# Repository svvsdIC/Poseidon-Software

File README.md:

# Poseidon-Master
Contains all Poseidon related files. Please make sure to commit to your branch rather than to master.

Note: all folders contain a README.md that can be edited by the respective teams using those folders to make them easy to navigate. If your team creates additional folders please add them to this file tree.

File tree:<br/>
* Mechanical<br/>
* Electrical<br/>
* Software<br/>
  * Lulu<br/>
    * Arduino<br/>
      * LuluArduino<br/>
        * Sketches<br/>
          * Poseidon<br/>
    * Pi<br/>
  * Nemo<br/>
    * Arduino<br/>
      * NemoArduino<br/>
        * Sketches<br/>
          * Poseidon<br/>
    * Pi<br/>
* Documentation<br/>
  * Design Documents<br/>
  * Operational Documentation<br/>

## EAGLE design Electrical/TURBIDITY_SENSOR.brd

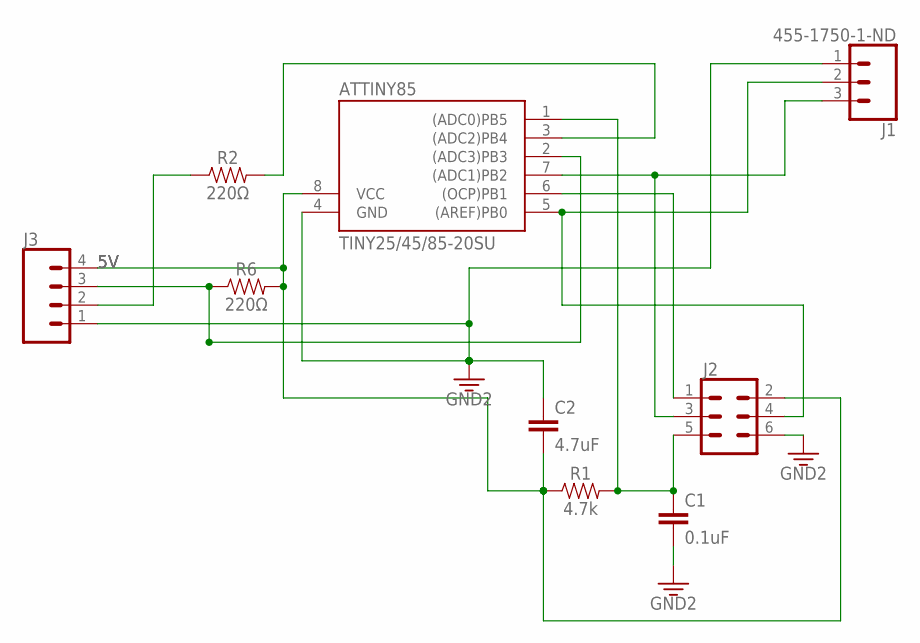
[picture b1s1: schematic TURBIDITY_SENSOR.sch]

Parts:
ATTINY85: TINY25/45/85-20SU; SOIC8
C1: 0.1uF; 0603
C2: 4.7uF; 1206
J1: 455-1750-1-ND; 1X03
J2: CONN_03X22X3_SILK_MALE_PTH; 2X3
J3: CONN_04; 1X04
R1: 4.7k; 0603
R2, R6: 220Ω; 0603

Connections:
5V: ATTINY85.8 (VCC), C2.2, J2.2, J3.4, R1.1, R6.2
DETECT: ATTINY85.2 ((ADC3)PB3), J3.3, R6.1
EMIT: ATTINY85.3 ((ADC2)PB4), R2.2
EMIT_OUT: J3.2, R2.1
GND: ATTINY85.4 (GND), C1.2, C2.1, J1.1, J2.6, J3.1
MISO: ATTINY85.6 ((OCP)PB1), J2.1
MOSI: ATTINY85.5 ((AREF)PB0), J1.2, J2.4
RESET: ATTINY85.1 ((ADC0)PB5), C1.1, J2.5, R1.2
SCK: ATTINY85.7 ((ADC1)PB2), J1.3, J2.3

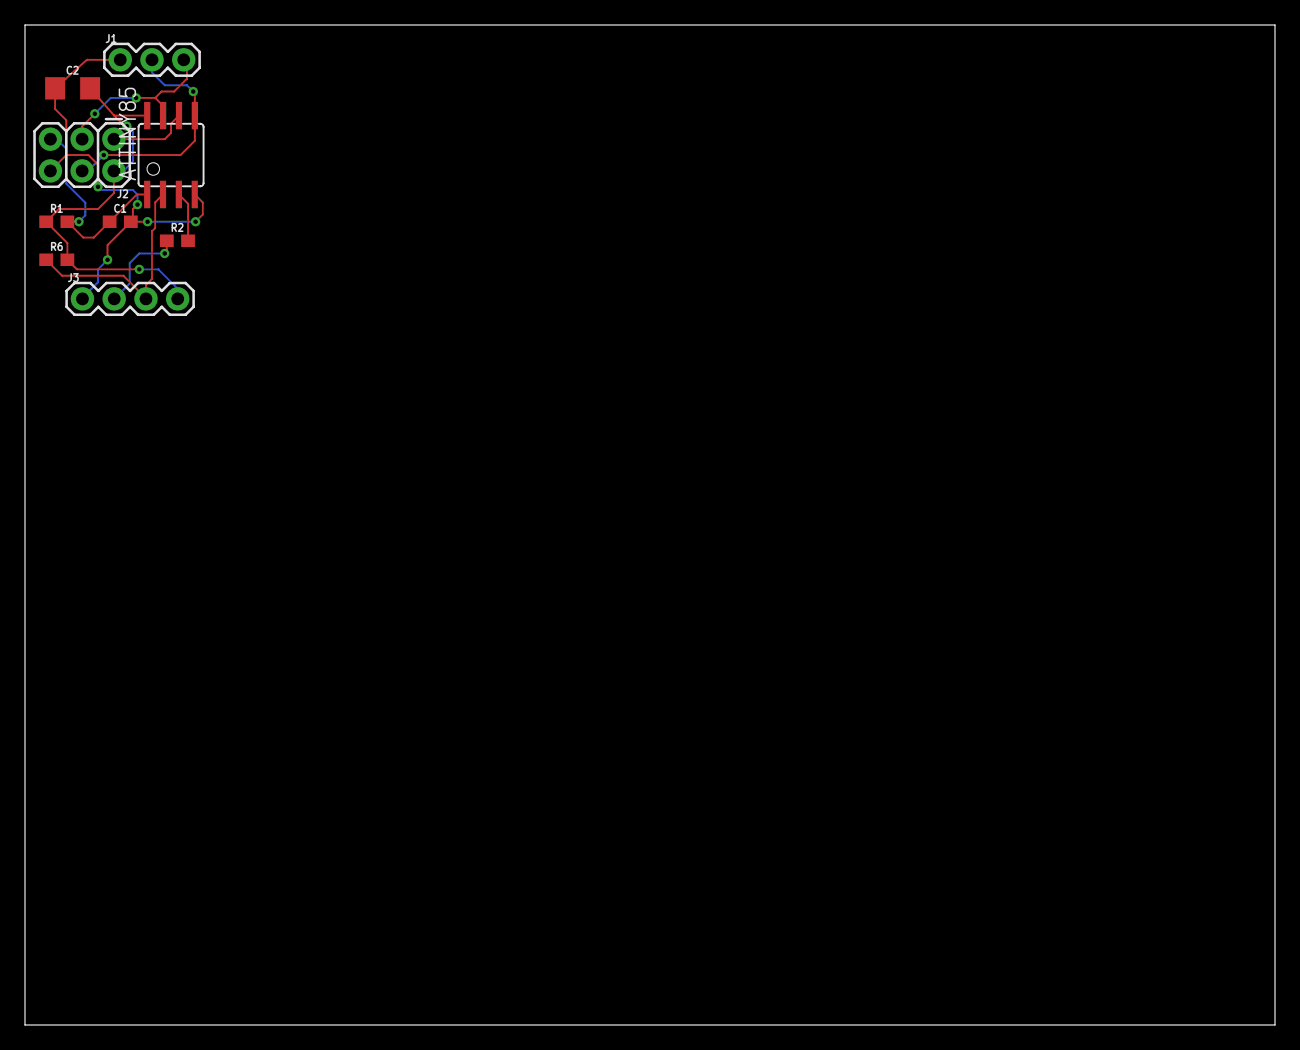
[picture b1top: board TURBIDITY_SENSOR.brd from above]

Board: 2 copper layers, 100.0 x 80.0 mm, 9 parts (0 on the bottom side), 9 nets.

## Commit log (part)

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2017-05-21 Added site specfic README, and enhanced .gitignore
2017-05-22 Ignore vim backup and swp files
2017-06-23 added poseidon-setup to be used after clone to setup additional npm dependencies
2017-11-10 Commiting Peter's work on pH sensor
2018-02-15 remove mjpeg -video plugin
2018-02-17 Changed ...js/button.js and .../button.html to pH_sensor After changing these needed to erase the cockpit cache (sudo rm -rf /usr/share/cockpit) and restart the cockpit and browser
2018-02-17 added correct hard coded url for video
2018-02-22 initial ORP and disOxy code
2018-02-22 Made ORP value change
2018-02-23 made conductivity sensor(still broken)
2018-02-26 b0be's attempt to put sensors in bottom dwelling <div>
2018-03-08 Moved the button and pH plugins to the bottom of the screen
2018-04-07 put widgets on bottom, made it run smooth
2018-04-07 made widgets look pretty
2018-04-07 Finished making a transparent background for the widgets.
2018-07-14 made the luminosity sensor. More work needs to be done because the code still has issues with button. peters fault
2018-09-22 Partial changes to button to make it temperature
2018-10-05 changes to the temperature sensor file thing because austin is complaining that I am doing it wrong
2018-10-18 made sidebysidefieldset look better
2018-11-01 The farenheit works now based of centigrade
2018-11-08 made surface temp folder. added temp arrow.
2018-11-16 Added color widget. Submerged color still needs mock data.
2019-01-25 Austin's latest.
2019-02-01 Created a bunch of random text files so folders upload
2019-02-07 Got rid of Hey.txt and added READMES
2019-02-08 Board Layout of Turbidity Sensor
    Sent to Pete for final verificaition
2019-02-08 Added X-drive
2019-02-08 Folder stuff for Davita?
2019-02-08 Merged repostories
2019-02-15 Moving Diamond Drive code to a more sensible place
    Moved from Lulu/X-Mega to Nemo/Arduino
2019-02-15 Update with slower serial polling
2019-02-20 remove unnecessary test code for figuring out server IP address
2019-03-08 Updated code, hopefully final draft
    Added analog support.
2019-03-21 Update ArduinoLight_P4
2019-04-04 Changed subColor shape to down triangle
2019-04-11 add for reference original OpenRov arduino code
2019-04-12 add the openrov-software-arduino code for reference
2019-05-23 Added surface directory which holds the code that sends surface info over bus
2019-06-09 Bump handlebars from 4.0.6 to 4.1.2 in /Software/Nemo/Pi
    Bumps [handlebars](https://github.com/wycats/handlebars.js) from 4.0.6 to 4.1.2.
    - [Release notes](https://github.com/wycats/handlebars.js/releases)
    - [Changelog](https://github.com/wycats/handlebars.js/blob/master/release-notes.md)
    - [Commits](https://github.com/wycats/handlebars.js/compare/v4.0.6...v4.1.2)
2019-06-13 Finished my first attempt at a library. Ready to fail.
2019-06-14 Deleted a line I forgot about.
2019-06-14 Create ArduinoLibraryCompleteCode
2019-06-20 .h file now matches order of .cpp file
2019-06-20 How could I forget to declare the variable type??? HOW...
2019-06-20 I think I know what's going on now, if I'm wrong then I will be extra sad. Please work code, I don't know if I could take it if you didn't.
2019-06-20 Semicolons are stupid ;
2019-06-21 Peter says I should fix everything before comitting.
2019-06-21 Final .cpp file, hopefully
2019-06-28 Fixed all the errors in the .cpp file
2019-08-23 changes to get serialport code working in raspberrypi board mode
2019-08-23 Bump ejs from 2.5.2 to 2.5.5 in /Software/Nemo/Pi
    Bumps [ejs](https://github.com/mde/ejs) from 2.5.2 to 2.5.5.
    - [Release notes](https://github.com/mde/ejs/releases)
    - [Changelog](https://github.com/mde/ejs/blob/master/CHANGELOG.md)
    - [Commits](https://github.com/mde/ejs/compare/v2.5.2...v2.5.5)
2019-08-23 Bump extend from 3.0.0 to 3.0.2 in /Software/Nemo/Pi
    Bumps [extend](https://github.com/justmoon/node-extend) from 3.0.0 to 3.0.2.
    - [Release notes](https://github.com/justmoon/node-extend/releases)
    - [Changelog](https://github.com/justmoon/node-extend/blob/master/CHANGELOG.md)
    - [Commits](https://github.com/justmoon/node-extend/compare/v3.0.0...v3.0.2)
2019-08-23 Bump stringstream from 0.0.5 to 0.0.6 in /Software/Nemo/Pi
    Bumps [stringstream](https://github.com/mhart/StringStream) from 0.0.5 to 0.0.6.
    - [Release notes](https://github.com/mhart/StringStream/releases)
    - [Commits](https://github.com/mhart/StringStream/compare/v0.0.5...v0.0.6)
2019-08-23 Bump brace-expansion from 1.1.6 to 1.1.11 in /Software/Nemo/Pi
    Bumps [brace-expansion](https://github.com/juliangruber/brace-expansion) from 1.1.6 to 1.1.11.
    - [Release notes](https://github.com/juliangruber/brace-expansion/releases)
    - [Commits](https://github.com/juliangruber/brace-expansion/compare/v1.1.6...1.1.11)
2019-08-23 Bump sshpk from 1.10.1 to 1.16.1 in /Software/Nemo/Pi
    Bumps [sshpk](https://github.com/joyent/node-sshpk) from 1.10.1 to 1.16.1.
    - [Release notes](https://github.com/joyent/node-sshpk/releases)
    - [Commits](https://github.com/joyent/node-sshpk/commits/v1.16.1)
2019-08-24 Bump debug in /Software/Nemo/Pi/src/plugins/notifications
    Bumps [debug](https://github.com/visionmedia/debug) from 2.6.1 to 2.6.9.
    - [Release notes](https://github.com/visionmedia/debug/releases)
    - [Changelog](https://github.com/visionmedia/debug/blob/2.6.9/CHANGELOG.md)
    - [Commits](https://github.com/visionmedia/debug/compare/2.6.1...2.6.9)
2019-08-24 Bump debug in /Software/Nemo/Pi/src/plugins/peer-view
    Bumps [debug](https://github.com/visionmedia/debug) from 2.6.1 to 2.6.9.
    - [Release notes](https://github.com/visionmedia/debug/releases)
    - [Changelog](https://github.com/visionmedia/debug/blob/2.6.9/CHANGELOG.md)
    - [Commits](https://github.com/visionmedia/debug/compare/2.6.1...2.6.9)
2019-08-24 Update debug requirement in /Software/Nemo/Pi/src/plugins/notifications
    Updates the requirements on [debug](https://github.com/visionmedia/debug) to permit the latest version.
    - [Release notes](https://github.com/visionmedia/debug/releases)
    - [Commits](https://github.com/visionmedia/debug/compare/2.2.0...4.1.1)
2019-08-24 Bump forwarded in /Software/Nemo/Pi/src/plugins/geomuxp
    Bumps [forwarded](https://github.com/jshttp/forwarded) from 0.1.0 to 0.1.2.
    - [Release notes](https://github.com/jshttp/forwarded/releases)
    - [Changelog](https://github.com/jshttp/forwarded/blob/master/HISTORY.md)
    - [Commits](https://github.com/jshttp/forwarded/compare/v0.1.0...v0.1.2)
2019-10-17 move poseidon arduino code into our library at appropriate place
2020-01-24 Added updated mock sensor code.
    All widgets are now working, next week I will work on integrating real sensors. Previously, this code was stored on my personal H:// drive.
2020-02-04 moved libraries for NemoArduino so they can be found by Arduino IDE/compiler
2020-02-05 Make Nemo Poseidon.ino work for minimal case
2020-02-08 Fixed board name in setArduino.sh for using mega2560
2020-02-08 fix typo in README.md
2020-02-08 fix yet another formatting typo in README.md, can't see them unitl pushed
2020-02-09 Fix fastCounter reset in CMock.cpp
2020-02-09 Fix fastCounter reset in CMock.cpp again
2020-02-14 Created new module for temperature sensor code.
2020-02-21 Luminosity + Temperature Sensor Integration
    This is the complete code base for running both the luminosity and temperature sensors, resolving earlier issues. In future I will work to streamline the code and remove relics/unneeded dependencies.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
2020-02-28 Deleted files with references to Servo.h which got rid of compiling error
2020-03-06 Add blink code to Blink Module
2020-03-26 .vscode files to compile arduino
2020-03-29 Working CBlink with hack to CCommand to allow testing without Pi
2020-04-09 Pablo's mac VScode setup
2020-04-10 changed the behavior of cblink, added protections
2020-04-16 Added useful Python program for reading writing to serial port, with or without CRC8 prepended.
2020-04-23 Added .vscode/c_cpp_profile.json file to git ignore
2020-04-24 Modified "SomeMod" module into "TemperatureSensor"
    Added some simple inital code to test!
2020-05-01 added sensing code to CTemperatureSensor.cpp
2020-05-17 fix prompting for baudrate and port
2020-05-22 Lulu portion of sending datagrams to Nemo using CBlink_ctrl
2020-05-30 commented out serial port debugging console.log statements
2020-05-30 add ";" to end of commands being sent to Nemo Pi
2020-05-31 fix mismatch of fast/slow variable names
2020-06-26 Started moving input pin code from maincontroller1.4.ino to CReceiver module
2020-06-26 most recent code
2020-07-09 Moved all Software file out of the Software directory and up to the project root
2020-07-09 Moved old code and utils
    * Arduino code we don't want to lose moved to achive/ on project root
    * Python utility scripts moved to new util/ on project root
2020-07-09 Move NemoArduino content up a level
2020-09-03 fix up crc calculation
2020-09-03 removed debugging logs
2020-09-03 use correct port for arduino-uno
2020-09-03 Moved CReceiver from rover to surface
2020-09-12 Revert "Seed ph module from Cmodule template"
    This reverts commit a0bfd4a52c009c703fcca377c0d6f24dabc44f18.
    We created some files as a way of demonstrating how a pull request
    works. These files don't really make any sense in the project, so
    this commit deletes those files.
2020-10-01 moved the surface arduino sketches to new location
2020-10-25 Start of CMotorController module
    This initial code includes the initialization and output structures copied from MainControl1.4.ino
2020-11-07 Move all code to temporary directory
2020-11-08 Move documented Arduino/Pi messages to project root
2020-11-12 Bring in PrintDebug() function to CCommand module
    The PrintDebug() function was originally written as part of the rover code. This brings
    in the changes to the top level root arduino directory
2020-11-12 Remove rover Arduino files
2020-11-12 Bring in CReceiver from surface code
2020-11-12 Bring in changes from surface modules
2020-11-19 fix output commands to terminate with ';'
2020-11-20 save progress 11/19/20
2021-01-02 No need to have an X-mega directory
2021-01-03 Remove the Servo library from libraries/ directory
    The Arduino Core includes a Servo library. The one in the libraries/ directory
    is redundant. After reviwing both implementations, there is not much difference.
    The implementaiton provided by the core is newer, but it does not provide any
    difference in implementation. It support some additional architectures and uses
    CPP standard types. It is an update of the same library.
2021-01-03 Disable all thruster configs
2021-01-15 initial code complete and started Common.h
2021-01-18 Make the default SysConfig implementation NOT have a thruster defined
2021-01-19 Move some source files we want to keep for now
    The first part of the code refactor required merging all of the code
    for the surface and the rover. There are a few files that have
    conflicting code. However, it is not entirely clear which version
    of the file should be kept.
    These files are stored in to the arduino_keep_for_now/ directory to allow
    for further review.
2021-01-19 Delete OpenROV2x.ino and add arduino.ino
    This file is the same as arduino/arduino.ino. There is no need to
    keep redundant files.
2021-01-22 add emum to common.h, and cleaned up CMotorControl code and got a clean compile
2021-02-04 Conditional compilation of timer register
2021-02-04 prodect define macros with parens
2021-02-19 Successfully uploaded CMotorControl to the board, error with static const arrays
2021-03-05 common.h updated
2021-03-18 Add outline for new output manager
2021-04-01 Changed the output values to send together
    Deleted the 4 different commands and now are only sending them once in a
    single command
2021-04-02 Changed the behavior of CMotorControl
    Changed CMotorControl to correctly read from CReceiver
    Added common.h some reason we didnt have it
2021-04-16 Cleaned up lulu.js using rover.js

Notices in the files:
parts and their libraries:
SparkFun-Capacitors: Licensing: Creative Commons ShareAlike 4.0 International - https://creativecommons.org/licenses/by-sa/4.0
